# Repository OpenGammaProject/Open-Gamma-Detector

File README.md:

# Open Gamma Detector

---

**This is the latest hardware revision 4.2 using the Pico 2! For older revisions, please have a look at the [other branches](https://github.com/OpenGammaProject/Open-Gamma-Detector/branches). A comparison between the 4.0 and 3.x hardware can be found [here](https://hackaday.io/project/185211-all-in-one-gamma-ray-spectrometer/log/225597-revision-40-status-report).**

**This project is also on [Hackaday.io](https://hackaday.io/project/185211-all-in-one-gamma-ray-spectrometer), where I post important project updates and other announcements!**

Open hardware for a hackable gamma spectrometer all-in-one device using a popular NaI(Tl) scintillation crystal and a silicon photomultiplier (SiPM). Extremely affordable design for a powerful DIY gamma spectroscopy setup with a total parts cost of around 200 USD if you get all the individual parts and assemble them on your own.

The detector uses a standard serial-over-USB and hardware UART connections so that it can be integrated into as many other projects as possible, for example data logging with a Raspberry Pi, weather stations, Arduino projects, etc. It includes both scintillation counter and multichannel analyzer (MCA) functions depending on how you want to use it.

<p align="center">
  
  <br>
  
</p>

If you want a more barebones version of the Open Gamma Detector to only count pulses or similar, you can have a look at the [Mini SiPM Driver](https://github.com/OpenGammaProject/Mini-SiD) board.

## Features

Here are some of the most important specs:

- Compact design: Total size 120 x 50 mm. Approx. 70.5 x 50 mm area for electronics and additional 49.5 x 50 mm to mount a scintillator.
- All-in-one: No external parts (e.g. sound card) required to record gamma spectra.
- Standalone spectra recordings on built-in flash.
- Easily programmable using drag-and-drop firmware files or the standard Arduino IDE.
- Low-voltage device: No HV needed like with photomultiplier tubes.
- Can use SiPMs in the voltage range of 27.5 V to 33.8 V.
- 4096 ADC channels with built-in 3 V voltage reference.
- Energy resolution of up to 7% @ 662 keV possible; highly dependent on your SiPM/scintillator assembly.
- Energy Mode: ~10 µs total dead time while measuring energy (default settings).
- Geiger Mode: ~1 µs total dead time without energy measurements (default settings).
- Low power consumption: ~15 mA @ 5 V with default firmware at normal background.
- Built-in ticker (buzzer) for audible pulse count rate output.
- Additional broken-out power pins and I2C, SPI and UART headers for custom parts (e.g. display, µSD card, etc.).
- Simple OLED support out of the box (SSD1306 and SH110x).
- Built-in True Random Number Generator.

## How To Get One

- You can check out the project on PCBWay (affiliate) and if you buy through their service, it supports the project a little, and doesn’t cost you anything extra.
- Otherwise, use a PCB manufacturer and an electronics distributor of your choice and proceed on your own. All the files you'll need can be found in this repo.
- If you don't want to deal with all of that, feel free to contact me. Just send me an e-mail and I can help you out with the process.

**You will also need to buy a SiPM (e.g. the MICROFC-60035-SMT-TR) and scintillator (NaI(Tl) recommended) separately at a distributor of your choice.** You might also want to grab one of the countless SiPM breakout boards I made.

## Working Principle

Here is a nice flow chart to describe how the device roughly works:

## Hardware

Hardware design has been done with [EasyEDA](https://easyeda.com/) and all the needed files for you to import the project as well as the schematic can be found in the `hardware` folder. There is also a Gerber file available for you to go directly to the PCB manufacturing step.

Detailed information about the hardware of the detector as well as the potentiometer settings and assembly can be found in the [hardware directory](/hardware/).

## Software

The software aims to be as simple as possible to understand and maintain. To achieve this I decided to use an off-the-shelf microcontroller - the [Raspberry Pi Pico 2](https://www.raspberrypi.com/products/raspberry-pi-pico-2/). This board can be programmed with the Arduino IDE over micro-USB and is powerful (dual core, fast ADC, plenty of memory, ...) enough for the purpose and also exceptionally cheap.

To program the Pico 2 and/or play around with the firmware, head to the [software directory](/software/). There you will also find documentation on the serial interface (!), display support, and much more.

## Troubleshooting and FAQ

Please have a look at [REFERENCE.md](REFERENCE.md) for some general guidance.

If this doesn't help you, feel free to reach out and create an issue or open a discussions thread.

## Example Spectra

Here is a small collection of example spectra I could make quickly without putting much effort into the detector settings (threshold, SiPM voltage, software tweaks). I'm using the [Tiny MicroFC Breakout](https://github.com/OpenGammaProject/Tiny-MicroFC-Carrier-Board) and just a single SiPM (which isn't the optimal setup actually). In addition, neither the electronics nor the scintillator and sample were shielded from EMI or background radiation whatsoever. So as you can see the detector is actually pretty robust in that regard.

Background spectrum (2h) with no samples:

Spectrum (2h) of two tiny (~5 g) LYSO scintillator showing two distinct gamma peaks (201.83, 306.78 keV) with an additional ~55 keV X-ray peak. The 307 keV peak has an energy resolution of ~14% in this case:

Spectrum (5min) of Am-241 commonly used in household ionization smoke detectors (e.g. in the US, no longer in the EU). Gamma peaks at 26.34 and 59.54 keV:

Spectrum (2h) of a small tea cup with pure Uraninite (also known as pitchblende) contents in its glaze. You can see all kinds of isotopes of the Uranium series including the Bi-214 peak at ~610 keV. Because they just used the pure Uraninite without any filtering whatsoever, there is also some U-235 in it and all the daughter radionuclides as well:

Spectrum (30min) of a Na-22 test source, about ~2 µCi made with a Rev.2 board (worse energy resolution than the latest version). You can see the 511 keV annihilation peak and the small 1275 keV gamma peak (much smaller due to limited NaI efficiency and small scintillator size for this energy) as well as the compton edge and continuum:

Spectrum (2h) of about 100 grams of mushrooms still containing the isotope Cs-137 from the Chernobyl disaster. You can clearly see the gamma peak at 662 keV and the ~32 keV X-ray peak. Resolution of the 662 keV peak was ~8.6%, using only a single SiPM and an old NaI scintillator:

---

**Here are some of the same spectra using a larger 1x1 inch scintillator rated at 6.9% @ 662 keV and a 2x2 SiPM array:**

Spectrum (1h) of the same mushroom sample from above. This time the resolution at the 662 keV Cs-137 was 7.7%, not bad!

Spectrum (1h) of a small batch of Lutetium(III) oxide. It contains Lu-176 just like the LYSO scintillator sample from above. Therefore it also has the same peaks, just a lot more clear now. The 307 keV peak now has an energy resolution of 11.5%.

## Known Limitations

1. ~~The Raspberry Pi Pico's ADC has some pretty [severe DNL issues](https://pico-adc.markomo.me/INL-DNL/#dnl) that result in four channels being much more sensitive (wider input range) than the rest. For now the simplest solution was to discard all four of them, by printing a `0` when any of them comes up in the measurement (to not affect the cps readings). You can turn this behavior off by using the `set correction` command. This is by no means perfect or ideal, but it works for now until this gets fixed in a later hardware revision of the RP2040 (wish us luck!).~~ Fixed by the Pico 2!
2. The power supply is **not** temperature corrected itself, meaning changes in the ambient temperature with a constant voltage affect the gain of the SiPM. This will naturally result in a different DC bias, energy range and S/N ratio. This effect is negligible around room temperature, though. The temperature dependence of the gain is -0.8%/°C (21°C) for the MicroFC SiPMs. **The latest [MicroFC SiPM carrier board](https://github.com/OpenGammaProject/MicroFC-SiPM-Carrier-Board) has automatic temperature compensation on-board however! So use that if you want to get the best performance out of it.**

## Some Ideas

### Coincidence Measurements

Using multiple detector boards with some firmware modifications it should be theoretically possible to implement a coincidence measurement feature. By respectively connecting the `VSYS`, `GND` and one of the broken-out pins to each other on both boards you have everything you need to get started. The pins would be used for an interrupt from the child detector to the parent to trigger a pulse if both timings coincide.

At the moment, though, I couldn't get a coincidence mode feature running due to some weird timing issues. There might be a firmware update in the future to implement this feature. If you have any ideas, let me know!

### Cooling the SiPM

During operation all the electronics including the SiPM naturally heat up ever so slightly. Due to the detector board (where most of the power is dissipated) not being directly connected to the SiPM self-heating is negligible, though. Therefore air or water cooling alone won't improve performance considerably, because it won't heat up much above ambient temps, if at all that is. However, you could cool the SiPM PCB with a Peltier module to sub-ambient temperatures. According to the [datasheet AND9770 (Figure 27)](https://www.onsemi.com/pub/Collateral/AND9770-D.PDF) every 10°C reduction in temperature decreases the dark count rate by 50%! But be sure to correct the SiPM voltage (overvoltage) in this case as it also changes with temperature.

Note that the required breakdown voltage of the SiPM increases linearly with 21.5 mV/°C, see the [C-Series SiPM Sensors Datasheet](https://www.onsemi.com/pdf/datasheet/microc-series-d.pdf). This means that you would also need to temperature correct the PSU voltage if you wanted to use it with considerably different temperatures.

### Shielding Background Radiation

Shielding the ambient background can be done ideally using a wide enough layer of lead (bricks) all around the detector with a thin layer of lower-Z material on the inside such as copper to avoid backscattering. The SiPM and the sample can then be put into the structure to get the best measurements possible (low background).

See Wikipedia: [Lead Castle](https://en.wikipedia.org/w/index.php?title=Lead_castle&oldid=991799816)

## Related Projects

This is a list of other awesome projects that are relevant or directly related to this one:

- [OpenDosimeter](https://opendosimeter.org/): A low-cost dosimeter with open-source hardware and software inspired heavily by the Open Gamma Detector.
- [CosmicWatch](http://www.cosmicwatch.lns.mit.edu/): A neat all-in-one device to detect muons. Completely open-source and designed for university students and schools. This project was the original inspiration to start with the Open Gamma Project.
- [OpenGammaKit](https://github.com/vikulin/OpenGammaKit/): Re-design of the Open Gamma Detector hardware using KiCAD, with additionally updated software for mobile use.

Check them out and let me know what you think. Special thanks to all of the contributors and the entire community for making this possible!

---

Thanks for reading.

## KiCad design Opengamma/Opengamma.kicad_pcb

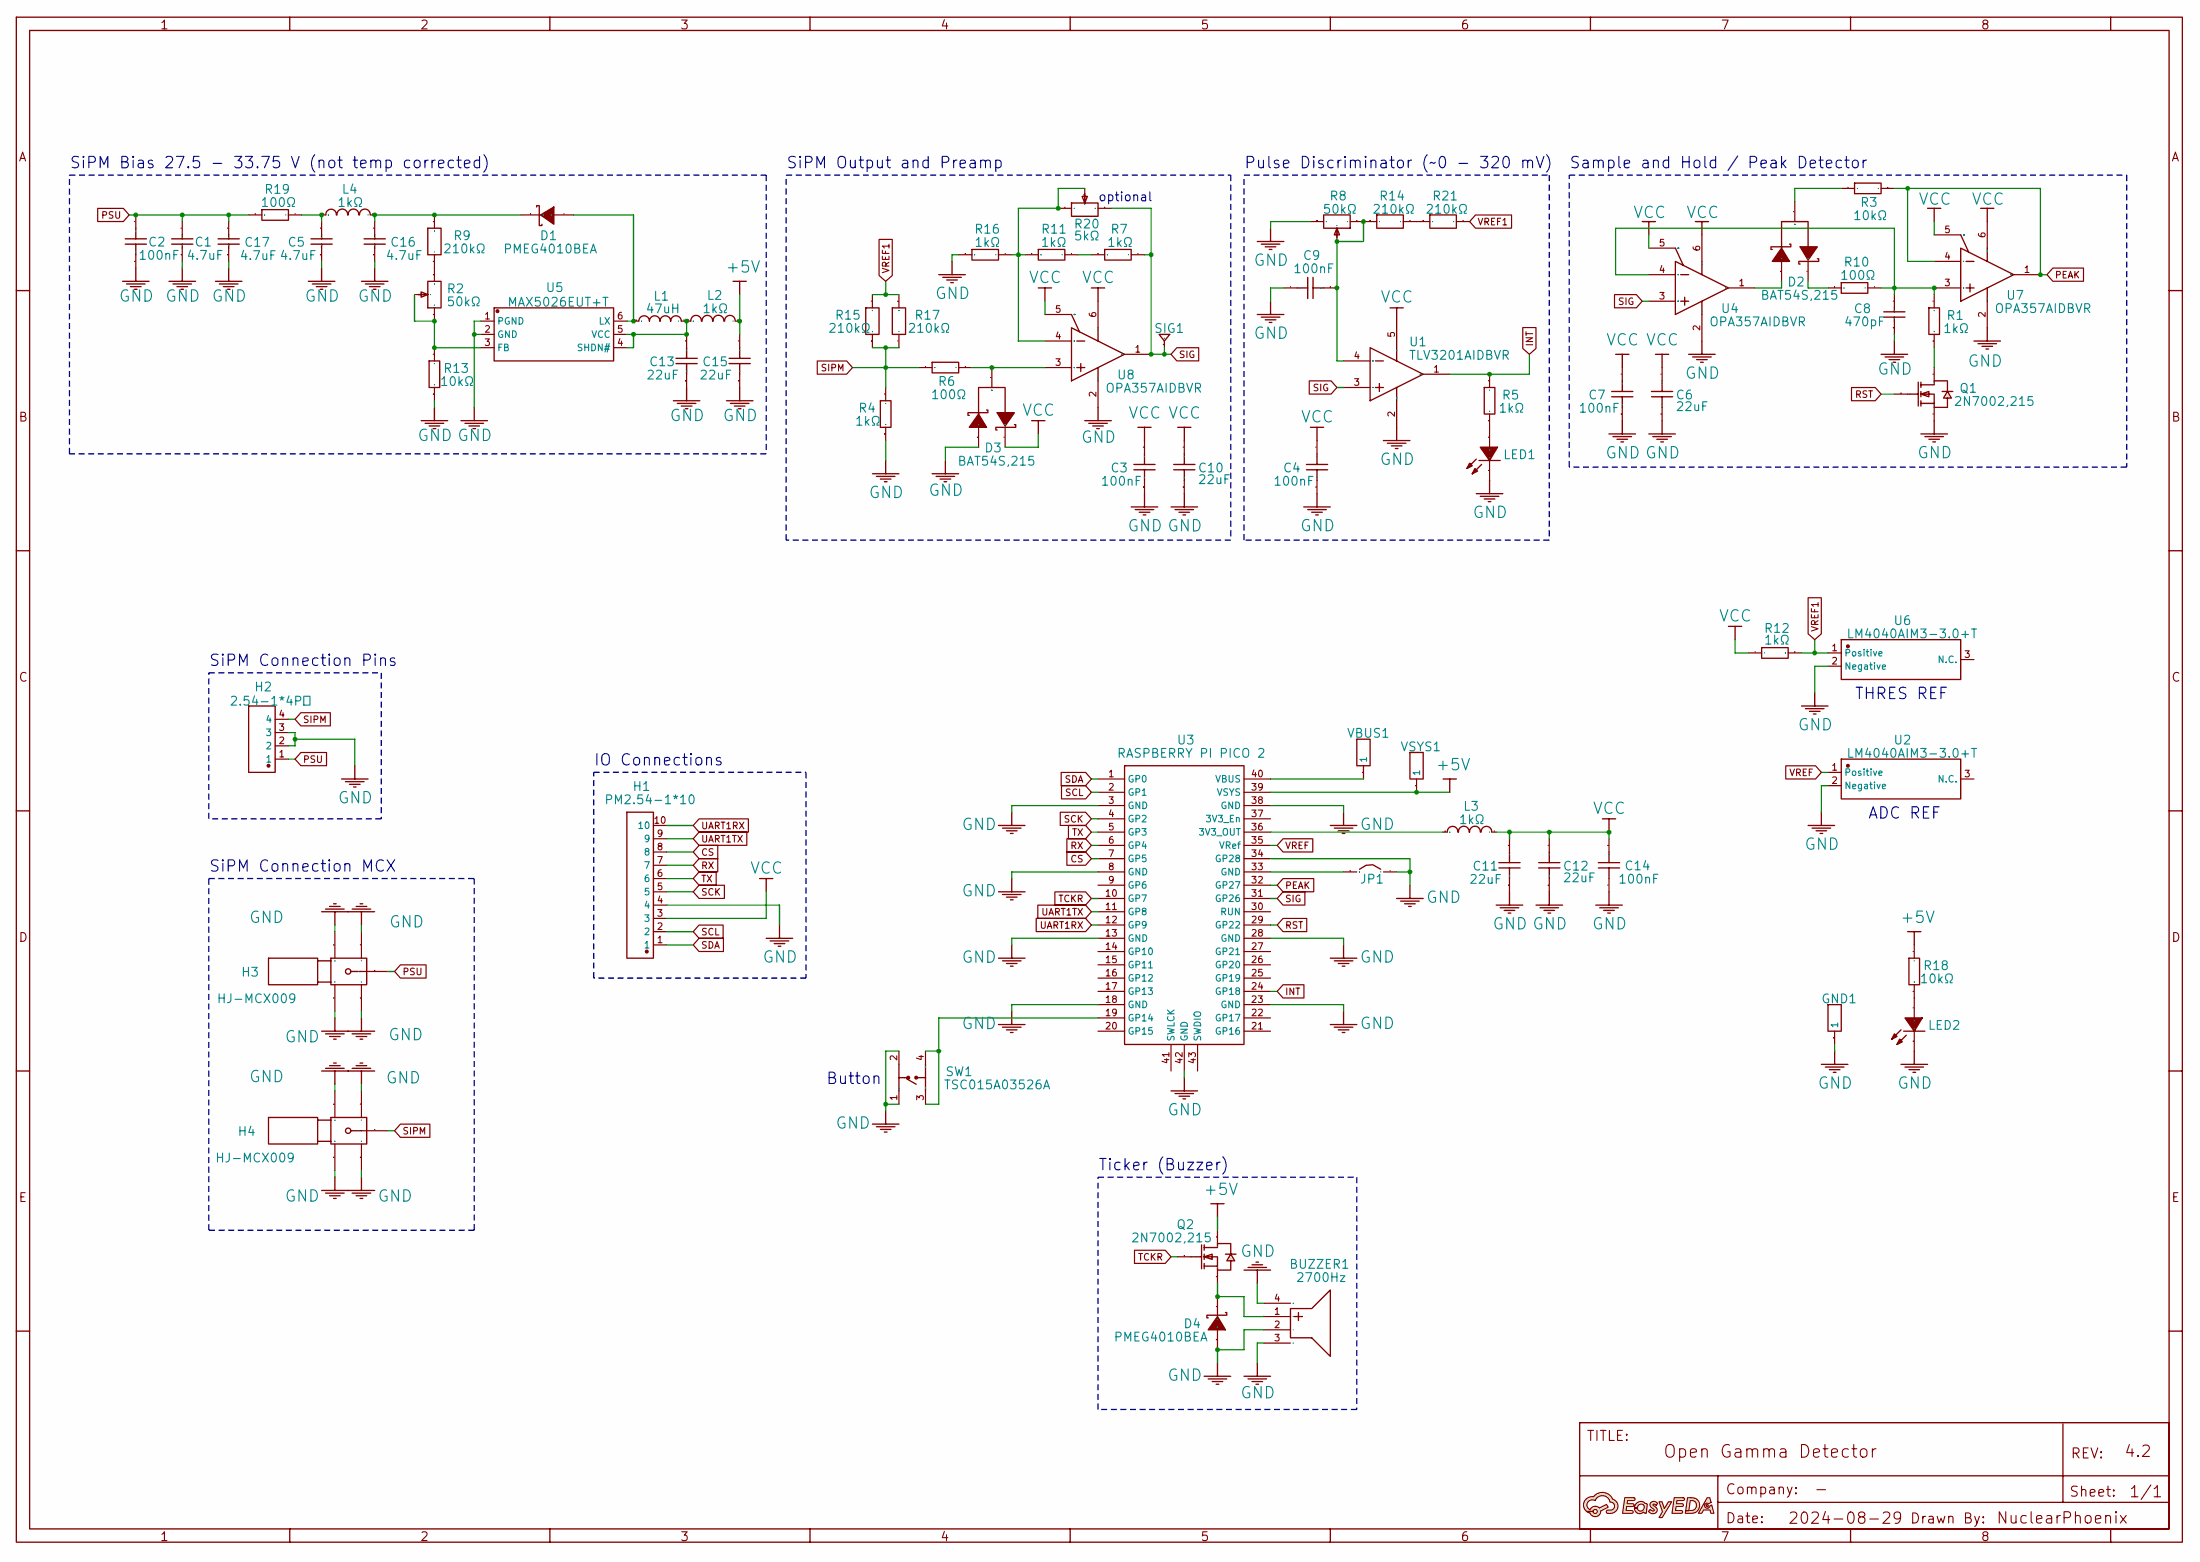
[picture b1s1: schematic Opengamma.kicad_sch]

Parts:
BUZZER1: 2700Hz; Manufacturer Part MLT-7525
C1, C5, C16, C17: 4.7uF; Manufacturer Part CL21A475KBQNNNE
C2, C3, C4, C7, C9, C14: 100nF; Manufacturer Part CL10B104KC8NNNC
C6, C10, C11, C12, C13, C15: 22uF; Manufacturer Part CL10A226MP8NUNE
C8: 470pF; Manufacturer Part ECHU1C471JX5
D1, D4: PMEG4010BEA; Manufacturer Part PMEG4010BEA,115
D2, D3: BAT54S,215; Manufacturer Part BAT54S,215
GND1: HDR-M-2.54_1x1
H1: PM2.54-1*10; Manufacturer Part PM2.54-1*10
H2: 2.54-1*4P母; Manufacturer Part 2.54-1*4P母
H3, H4: HJ-MCX009; Manufacturer Part HJ-MCX009
JP1: Jumper
L1: 47uH; Manufacturer Part NRS4018T470MDGJ
L2, L3, L4: 1kΩ; Manufacturer Part BLM18KG102SN1D
LED1, LED2: LTST-C190KGKT; Manufacturer Part LTST-C190KGKT
NO1: NO; Manufacturer Part ?
Q1, Q2: 2N7002,215; Manufacturer Part 2N7002,215
R1, R4, R5, R7, R11, R12, R16: 1kΩ; Manufacturer Part ARG03BTC1001
R2, R8: 50kΩ; Manufacturer Part 3296W-1-503LF
R3, R13, R18: 10kΩ; Manufacturer Part ARG03FTC1002
R6, R10, R19: 100Ω; Manufacturer Part 0603WAF1000T5E
R9, R14, R15, R17, R21: 210kΩ; Manufacturer Part TC0325D2103T5H
R20: 5kΩ; Manufacturer Part 3314J-1-502E
SIG1: TEST-POINT
SW1: TSC015A03526A; Manufacturer Part TSC015A03526A
U1: TLV3201AIDBVR; Manufacturer Part TLV3201AIDBVR
U2, U6: LM4040AIM3-3.0+T; Manufacturer Part LM4040AIM3-3.0+T
U3: RASPBERRY PI PICO 2; Manufacturer Part SC1631
U4, U7, U8: OPA357AIDBVR; Manufacturer Part OPA357AIDBVR
U5: MAX5026EUT+T; Manufacturer Part MAX5026EUT+T
VBUS1: HDR-M-2.54_1x1
VSYS1: HDR-M-2.54_1x1

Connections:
+5V: C15.2, L2.2, Q2.3 (D), R18.2, U3.39 (VSYS), VSYS1.1
CS: H1.8, U3.7 (GP5)
GND: BUZZER1.2 (-), BUZZER1.3, BUZZER1.4, C1.1, C2.1, C3.1, C4.1, C5.1, C6.1, C7.1, C8.1, C9.2, C10.1, C11.1, C12.1, C13.1, C14.2, C15.1, C16.1, C17.1, D3.1 (A), D4.2 (A), GND1.1, H1.4, H2.2, H2.3, H3.1, H3.2, H3.3, H3.4, H4.1, H4.2, H4.3, H4.4, JP1.2, LED1.1 (-), LED2.1 (-), Q1.2 (S), R4.1, R8.1, R13.1, R16.1, SW1.1, SW1.2, U1.2 (GND), U2.2 (Negative), U3.3 (GND), U3.8 (GND), U3.13 (GND), U3.18 (GND), U3.23 (GND), U3.28 (GND), U3.34 (GP28), U3.38 (GND), U3.42 (GND), U4.2 (V-), U5.1 (PGND), U5.2 (GND), U6.2 (Negative), U7.2 (V-), U8.2 (V-)
INT: R5.2, U1.1 (OUT), U3.24 (GP18)
unnamed: BUZZER1.1 (+), D4.1 (K), Q2.2 (S)
unnamed: C5.2, L4.1, R19.2
unnamed: D1.2 (A), L1.1, U5.6 (LX)
unnamed: C16.2, D1.1 (K), L4.2, R9.1
unnamed: D2.1 (A), U4.1 (OUT)
unnamed: D2.3 (AK), R3.2
unnamed: D2.2 (K), R10.1
unnamed: D3.3 (AK), R6.2, U8.3 (IN+)
unnamed: JP1.1, U3.33 (GND)
unnamed: LED1.2 (+), R5.1
unnamed: LED2.2 (+), R18.1
unnamed: Q1.3 (D), R1.1
unnamed: R2.1, R9.2
unnamed: R7.1, R11.2
unnamed: R14.2, R21.1
unnamed: C9.1, R8.2, R8.3, R14.1, U1.4 (IN-)
unnamed: L3.1, U3.36 (3V3_OUT)
unnamed: SW1.3, SW1.4, U3.19 (GP14)
unnamed: U3.40 (VBUS), VBUS1.1
unnamed: C8.2, R1.2, R10.2, U4.4 (IN-), U7.3 (IN+)
unnamed: R2.2, R2.3, R13.2, U5.3 (FB)
unnamed: C13.2, L1.2, L2.1, U5.4 (SHDN#), U5.5 (VCC)
unnamed: R11.1, R16.2, R20.2, R20.3, U8.4 (IN-)
PEAK: R3.1, U3.32 (GP27), U7.1 (OUT), U7.4 (IN-)
PSU: C1.2, C2.2, C17.2, H2.1, H3.5, R19.1
RST: Q1.1 (G), U3.29 (GP22)
RX: H1.7, U3.6 (GP4)
SCK: H1.5, U3.4 (GP2)
SCL: H1.2, U3.2 (GP1)
SDA: H1.1, U3.1 (GP0)
SIG: R7.2, R20.1, SIG1.1, U1.3 (IN+), U3.31 (GP26), U4.3 (IN+), U8.1 (OUT)
SIPM: H2.4, H4.5, R4.2, R6.1, R15.1, R17.2
TCKR: Q2.1 (G), U3.10 (GP7)
TX: H1.6, U3.5 (GP3)
UART1RX: H1.10, U3.12 (GP9)
UART1TX: H1.9, U3.11 (GP8)
VCC: C3.2, C4.2, C6.2, C7.2, C10.2, C11.2, C12.2, C14.1, D3.2 (K), H1.3, L3.2, R12.2, U1.5 (VCC), U4.5 (ENABLE), U4.6 (V+), U7.5 (ENABLE), U7.6 (V+), U8.5 (ENABLE), U8.6 (V+)
VREF: U2.1 (Positive), U3.35 (VRef)
VREF1: R12.1, R15.2, R17.1, R21.2, U6.1 (Positive)

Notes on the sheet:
SiPM Bias 27.5 - 33.75 V (not temp corrected)
THRES REF
SiPM Connection MCX
optional
Button
Pulse Discriminator (~0 - 320 mV)
SiPM Connection Pins
SiPM Output and Preamp
Ticker (Buzzer)
ADC REF
Sample and Hold / Peak Detector
IO Connections

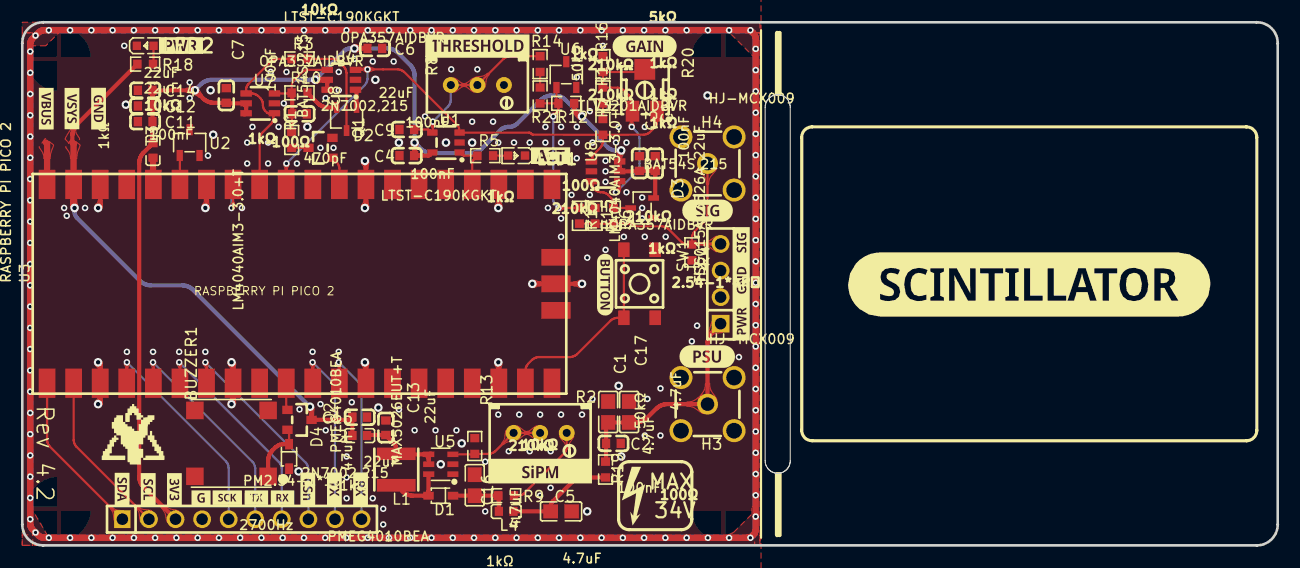
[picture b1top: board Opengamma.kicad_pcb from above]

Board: 2 copper layers, 120.0 x 50.0 mm, 65 parts (1 on the bottom side), 42 nets.

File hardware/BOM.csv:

ID;Name;Designator;Footprint;Quantity;Manufacturer Part;Manufacturer;Supplier;Supplier Part;Price
1;2700Hz;BUZZER1;BUZ-SMD_4P-L7.5-W7.5-P7.59-TL;1;MLT-7525;华能;LCSC;C95299;0.226
2;PMEG4010BEA;D1,D4;SOD-323_L1.8-W1.3-LS2.5-RD;2;PMEG4010BEA,115;Nexperia(安世);LCSC;C36975;1.315
3;PM2.54-1*10;H1;HDR-TH_10P-P2.54-V-F;1;PM2.54-1*10;ZHOURI(洲日);LCSC;C5116489;0.106
4;2.54-1*4P母;H2;HDR-TH_4P-P2.54-V-F;1;2.54-1*4P母;BOOMELE(博穆精密);LCSC;C2718488;0.047
5;HJ-MCX009;H3,H4;ANT-TH_L6.0-W6.0_MCX-KE;2;HJ-MCX009;皇捷;LCSC;C2904906;0.724
6;47uH;L1;IND-SMD_L4.0-W4.0_NR4018T;1;NRS4018T470MDGJ;TAIYO YUDEN(太诱);LCSC;C222886;0.126
7;2N7002,215;Q1,Q2;SOT-23_L2.9-W1.3-P1.90-LS2.4-BR;2;2N7002,215;Nexperia(安世);LCSC;C65189;0.161
8;1kΩ;R1,R4,R5,R7,R11,R12,R16;R0603;7;ARG03BTC1001;Viking(光颉);LCSC;C309080;0.019
9;100Ω;R6,R10,R19;R0603;3;0603WAF1000T5E;UNI-ROYAL(厚声);LCSC;C22775;0.001
10;210kΩ;R9,R14,R15,R17,R21;R0603;5;TC0325D2103T5H;UNI-ROYAL(厚声);LCSC;C517422;0.023
11;TSC015A03526A;SW1;SW-SMD_4P-L4.5-W4.5-P3.00-LS6.8;1;TSC015A03526A;BZCN(博众电气);LCSC;C2888900;0.011
12;TLV3201AIDBVR;U1;SOT-23-5_L3.0-W1.7-P0.95-LS2.8-BR;1;TLV3201AIDBVR;TI(德州仪器);LCSC;C105188;0.402
13;LM4040AIM3-3.0+T;U2,U6;SOT-23-3_L2.9-W1.6-P1.90-LS2.8-BR;2;LM4040AIM3-3.0+T;ADI(亚德诺)/MAXIM(美信);LCSC;C143326;1.381
14;RASPBERRY PI PICO 2;U3;PI-PICO-SMD;1;SC1631;Raspberry Pi;Mouser;358-SC1631;
15;4.7uF;C1,C5,C16,C17;C0805;4;CL21A475KBQNNNE;SAMSUNG(三星);LCSC;C98192;0.02
16;BAT54S,215;D2,D3;SOT-23-3_L3.0-W1.7-P0.95-LS2.9-BR;2;BAT54S,215;Nexperia(安世);LCSC;C47546;0.016
17;LTST-C190KGKT;LED1,LED2;LED0603-RD;2;LTST-C190KGKT;LITEON(光宝);LCSC;C125094;0.015
18;10kΩ;R3,R13,R18;R0603;3;ARG03FTC1002;Viking(光颉);LCSC;C217687;0.007
19;22uF;C6,C10,C11,C12,C13,C15;C0603;6;CL10A226MP8NUNE;SAMSUNG(三星);LCSC;C86295;0.015
20;100nF;C2,C3,C4,C7,C9,C14;C0603;6;CL10B104KC8NNNC;SAMSUNG(三星);LCSC;C15725;0.006
21;50kΩ;R2,R8;RES-ADJ-TH_3296W;2;3296W-1-503LF;BOURNS;LCSC;C83686;0.712
22;OPA357AIDBVR;U4,U7,U8;SOT-23-6_L2.9-W1.6-P0.95-LS2.8-BR;3;OPA357AIDBVR;TI(德州仪器);LCSC;C139385;1.568
23;MAX5026EUT+T;U5;SOT-23-6_L2.9-W1.6-P0.95-LS2.8-BL;1;MAX5026EUT+T;ADI(亚德诺)/MAXIM(美信);LCSC;C87603;1.696
24;470pF;C8;C0603;1;ECHU1C471JX5;PANASONIC(松下);LCSC;C178419;0.262
25;1kΩ;L2,L3,L4;L0603;3;BLM18KG102SN1D;muRata(村田);LCSC;C160982;0.017

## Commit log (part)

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2020-10-18 add hardware files
2020-10-18 move hardware
2020-10-18 add some info
2020-10-18 add software
2020-11-02 add content sections
2020-11-08 Create placeholder
2020-11-08 add files
2020-11-08 add python requirements
2020-11-08 format python scripts
2020-11-08 add software info
2020-12-25 add background shielding + cooling sections
2021-04-18 add very simple serial interface
2021-04-18 misc working changes
2021-05-11 cleanup and simplify detector software
2021-05-11 cleanup
2021-05-13 revert stupid change
2021-07-21 add disclaimer
2021-09-21 add raspberry pi pico note
2021-10-18 add chart
2021-10-20 fix for dark mode
2021-11-20 add pico script
2021-11-20 remove python scripts
2021-11-20 rename
2021-11-20 update text
2021-11-20 update software
2021-11-20 add teaser image
2021-12-03 add badge
2021-12-04 [ImgBot] Optimize images
    *Total -- 119.67kb -> 82.81kb (30.8%)
    /docs/lu-176.png -- 70.65kb -> 42.60kb (39.7%)
    /docs/flow.drawio.png -- 49.01kb -> 40.21kb (17.96%)
2021-12-04 update plot
2022-02-22 update detector files
2022-02-22 new SiPM mount files
2022-02-23 [ImgBot] Optimize images
    *Total -- 320.89kb -> 171.71kb (46.49%)
    /docs/am-241.png -- 56.62kb -> 23.46kb (58.57%)
    /docs/pcb_back.png -- 59.97kb -> 32.17kb (46.35%)
    /docs/lu-176.png -- 78.05kb -> 44.23kb (43.34%)
    /docs/pcb_front.png -- 126.26kb -> 71.85kb (43.09%)
2022-02-23 [ImgBot] Optimize images
    /docs/flow.drawio.png -- 35.64kb -> 12.09kb (66.08%)
2022-02-23 remove gitignore
2022-02-24 add EOL char for Gamma MCA
2022-02-27 add scintillator assembly
2022-02-27 add key features
2022-03-06 add spectrum
2022-03-07 change img layout
2022-03-26 add serial commands
2022-04-01 add geiger mode
2022-04-14 misc event code changes
2022-04-14 discard non-linear adc values due to dnl
2022-04-18 set max pin output current
2022-04-23 add DNL issue
2022-05-07 small fixes
2022-05-07 new SiPM carrier board!
2022-05-16 remove SiPM carrier hardware
    moved to https://github.com/Open-Gamma-Project/SiPM-Carrier-Board
2022-06-30 update hackaday info
2022-07-01 misc layout and text changes
2022-07-01 add use cases
2022-07-01 fix firmware name
2022-07-01 slight changes in DNL note
2022-07-02 small misc changes
2022-07-03 unzip gerber
2022-07-03 Use UTF-8 encoding on BOM.csv
    Kitspace can't deal with UTF-16 BOMs yet
2022-07-04 fix cps buffer overflowing and crashing
2022-07-05 change pins for new board rev
2022-07-05 board revision 2
2022-07-05 update LYSO spectrum
2022-07-05 add remark on PCB size
2022-07-05 [ImgBot] Optimize images
    *Total -- 273.98kb -> 140.26kb (48.81%)
    /docs/flow.drawio.png -- 33.33kb -> 10.44kb (68.69%)
    /docs/pcb_back.png -- 48.30kb -> 22.79kb (52.81%)
    /docs/pcb_front.png -- 126.35kb -> 69.95kb (44.64%)
    /docs/lu-176.png -- 65.99kb -> 37.08kb (43.81%)
2022-07-08 add assembled boards note
2022-07-08 add background spectrum
2022-07-08 add space
2022-07-09 [ImgBot] Optimize images
    *Total -- 130.94kb -> 76.33kb (41.71%)
    /docs/bg.png -- 61.04kb -> 34.73kb (43.11%)
    /docs/lu-176-new.png -- 69.90kb -> 41.60kb (40.48%)
2022-07-30 add optional parts info
2022-08-13 Clarify issue #15
2022-08-18 version 2.1.0
    changelog:
    - remove unused Arduino Pico Analog Correction lib
    - add auto resets of the S&H circuit to help with 50 HZ mains
    interference when not shielded
    - small misc changes
2022-08-18 update detector commands
2022-08-19 remove compiled file
    oops
2022-08-19 slight revision changes
    Changelog:
    - Change inductor orientation for best EMI
    - R3 is now 1k! This fixes an old issue with noise at low energies
    - "Optional" parts markings in the schematic
    - New spectra
    - New images
2022-08-19 fix tab
2022-08-24 firmware v2.2.0
    changelog:
    - persistent settings: saving and loading from flash
    - add command to reset the settings
    - more detailed serial command interactions
    - fix temperature readings
    - add setting for the meas averaging
2022-08-25 add link to shop page
2022-09-02 add image for poti controls
2022-09-22 fix encoding
2022-09-22 add hardware watchdog
2022-09-26 update external shops and links
2022-09-29 add new image
2022-09-29 clarify dead time
2022-09-30 fix URL
2022-10-09 add Na-22 spectrum
2022-10-09 add coincidence mode section
2022-10-09 [ImgBot] Optimize images
    *Total -- 1,170.45kb -> 1,077.26kb (7.96%)
    /docs/na-22.png -- 58.01kb -> 32.49kb (44%)
    /docs/controls.jpg -- 123.30kb -> 115.03kb (6.71%)
    /docs/img2.jpg -- 989.14kb -> 929.74kb (6.01%)
2022-10-15 add oled support
2022-10-15 punctuation
2022-10-16 auto refresh oled data
2022-10-17 add display command
2022-10-26 bump firmware
2022-10-26 add firmware files
2022-10-28 add UF2 with 3.0 voltage reference
2022-11-02 add new todo
2022-11-02 small grammar changes and typos
2022-11-05 add overclocked pico firmware
2022-11-05 add sipm to intro text
2022-11-07 - fix crashes after some time with auto-enabled display, which would activate although there's not display
    - fix events not added in geiger mode
2022-11-07 autoformat
2022-11-12 faster display refresh
2022-11-12 FW version 2.3.4
2022-11-21 add 3D print case files
2022-11-21 add attribution
2022-11-21 add 3D-printable enclosure text
2022-11-21 add link to ViewSTL
2022-11-27 Firmware update 2.4.0
    - Add True Random Number Generator.
    - Add function to read settings.
    - Move meta-data reading (like temperature, Vsys, etc.) to "read info"
    command.
2022-11-27 fix indentation
2022-12-01 add reduced height versions
2022-12-01 TRNG disclaimer
2022-12-03 FW Update 2.5.0
    Changelog:
    - Change SimpleShell to SimpleShell_Enhanced
    - Complete Serial shell re-design
    - Add TRNG number storage
    - Add delay time serial setting
    - Some other small misc changes
2022-12-03 fix default vref
2022-12-03 add display issue link
2022-12-04 add dead time to info
2022-12-04 change fsinfo stats
2022-12-17 fix Vref
2022-12-21 [ImgBot] Optimize images
    *Total -- 193.16kb -> 170.79kb (11.58%)
    /docs/gamma_mca.png -- 101.91kb -> 83.30kb (18.26%)
    /docs/inside_box.jpg -- 91.25kb -> 87.49kb (4.12%)
2022-12-21 add tindie store link
2022-12-21 add OSHW cert badge
2022-12-30 add FW 2.5.2 files
2023-01-11 Stop filtering out PCB services in kitspace.yaml
2023-01-16 Fix URLs
2023-02-05 move oshwa link
2023-02-19 Fix display crashes
    Problem was the event_int function was possibly using the ADC _while_ the temp reading was going and this crashed the device.
2023-02-19 switch to bool
    Programmed too much in TS LOL
2023-02-19 FW version 2.5.3
2023-02-19 remove old FW files
2023-02-22 add total cost estimate
2023-02-26 enable strict checking
2023-03-01 FW for HW Rev 3.0
2023-03-01 add degree symbol
2023-03-08 hardware revision 3
2023-04-07 change intro text
2023-04-10 Fix #31
    Add Adafruit lib
2023-04-11 re-add image
2023-04-11 minor fixes
2023-04-11 add FW files
2023-04-11 update images
2023-04-11 remove space
2023-04-11 fix line break
2023-04-12 fix spectra description
    Some errors and old info
2023-04-12 add comparison post
2023-04-12 Update text on SiPM/scintillator size
2023-04-12 add OLED image
2023-04-16 update some comments
2023-04-16 update thumbnails
2023-04-18 add ring buffer for display cps
2023-04-18 fix comment
2023-04-19 update OSHWA cert
2023-04-19 [ImgBot] Optimize images
    *Total -- 3,574.95kb -> 3,155.38kb (11.74%)
    /docs/pcb_back.png -- 58.65kb -> 29.79kb (49.2%)
    /docs/pcb_front.png -- 109.66kb -> 58.35kb (46.79%)
    /docs/am-241.png -- 52.39kb -> 28.76kb (45.11%)
    /docs/bg.png -- 57.18kb -> 32.95kb (42.39%)
    /docs/glaze.png -- 63.96kb -> 38.20kb (40.27%)
2023-04-20 add 3D files
2023-04-21 Add Mini SiD reference
2023-04-21 FW 3.1.0
2023-04-22 Fixed typos, added link to vendors
2023-04-27 add array board references
2023-04-27 try to improve INT performance
2023-04-27 add BOOTSEL button switch
2023-04-29 FW 3.2.0
2023-04-29 update UF2 files
2023-05-06 add FW version 3.2.1
2023-05-15 add ticker feature
    also add debug info such as power-on hours and power cycles
2023-05-15 add v3.3.0 FW files
2023-05-15 add example ticker setting
2023-05-18 decrease buffer load
2023-05-18 add new FW files
2023-05-18 default SSD1306 display
2023-06-03 add Gamma MCA video
2023-06-07 convert text to SVG
2023-06-07 [ImgBot] Optimize images
    /docs/flow.drawio.svg -- 155.78kb -> 127.93kb (17.88%)
2023-07-06 update todo list
    there will be some changes soon ;)
2023-07-07 add FW 3.5.0 files
2023-07-07 add OpenGamma logo
2023-07-07 upload fixed FW files
2023-07-23 add version 3.5.1
2023-07-23 drop statistical, long live RunningMedian
2023-07-26 add temp compensation
2023-08-16 change 'read spectrum' output
2023-08-16 upload FW version 3.5.2
2023-08-19 add new case
2023-09-13 [ImgBot] Optimize images
    *Total -- 14,391.29kb -> 13,527.97kb (6%)
    /docs/mushrooms.png -- 74.44kb -> 46.51kb (37.53%)
    /docs/oshw.svg -- 13.54kb -> 12.54kb (7.39%)
    /docs/enclosure_empty2.jpg -- 3,407.81kb -> 3,201.28kb (6.06%)
    /docs/enclosure_panel1.jpg -- 3,524.37kb -> 3,311.37kb (6.04%)
    /docs/enclosure_empty1.jpg -- 3,478.40kb -> 3,268.17kb (6.04%)
2023-09-19 decrease OSHW size
2023-11-27 add rev 4 alpha sketch
2023-11-27 update screenshots to rev 4
2023-11-28 add hackaday posts
2023-12-02 add rev 4 to compat list
2023-12-02 update HW README
2023-12-02 add section on the onboard ACT LED
2023-12-02 update reference
2023-12-02 fix command description
2023-12-02 add FW 4.0.0 files
2023-12-02 rename files
2023-12-02 fix wrong state PS_PIN
2023-12-02 update software README
2023-12-02 update path
2023-12-02 add image caption
2023-12-02 update disclaimer
2023-12-03 update example spectra
2023-12-03 update uraninite desc
2023-12-03 [ImgBot] Optimize images
    *Total -- 666.42kb -> 400.29kb (39.93%)
    /docs/pcb_back.png -- 81.95kb -> 44.19kb (46.08%)
    /docs/am-241.png -- 47.93kb -> 26.76kb (44.18%)
    /docs/pcb_front.png -- 117.35kb -> 67.66kb (42.34%)
    /docs/bg.png -- 53.93kb -> 31.23kb (42.09%)
    /docs/lu-176.png -- 69.06kb -> 41.59kb (39.77%)
2023-12-06 change default averaging value
2023-12-06 bump version
2023-12-09 update OSHWA mark
2023-12-09 improve spectrometer response at high count rates
2023-12-10 misc changes
2023-12-27 add higher res spectra
2024-01-03 update ArduinoJSON support
2024-01-14 add notes on SiPM connection
2024-01-16 [ImgBot] Optimize images
    *Total -- 1,241.80kb -> 1,043.24kb (15.99%)
    /docs/pcb_back.png -- 80.57kb -> 42.92kb (46.73%)
    /docs/bg.png -- 58.20kb -> 34.59kb (40.57%)
    /docs/lu-176-advanced.png -- 57.14kb -> 34.80kb (39.09%)
    /docs/mushrooms.png -- 70.65kb -> 43.78kb (38.04%)
    /docs/mushrooms-advanced.png -- 57.21kb -> 35.76kb (37.49%)
2024-01-17 add info about buttons
2024-01-17 update specs
2024-01-17 add press duration
2024-01-18 update photos
2024-01-18 remove todo
2024-01-18 Remove part shortage limitation
2024-01-19 add FS spectrum recordings
2024-01-20 remove old comments
2024-01-20 add 4.2.0 FW files
2024-01-21 ignore build dir
2024-01-21 optimize if statements
2024-01-21 optimize adc bin number
2024-02-01 add note on forward compat to rev 4
2024-02-01 fix formatting
2024-02-02 add recording space warning
2024-02-26 fix #53
2024-03-02 update description
2024-03-04 add display default state note
2024-03-14 Update notes on saturation and the ACT LED
2024-03-29 add rev 4.1 files
2024-03-29 [ImgBot] Optimize images
    *Total -- 341.75kb -> 199.00kb (41.77%)
    /docs/pcb_back.png -- 81.21kb -> 43.25kb (46.74%)
    /docs/pcb_front.png -- 131.72kb -> 74.37kb (43.54%)
    /docs/controls.png -- 128.82kb -> 81.38kb (36.82%)
2024-06-04 add email support note
2024-06-05 add FW 4.2.2
    No changes, only updated arduino-pico for the latest LittleFS (file system) version.
2024-08-10 add Na-22 spectrum duration
2024-08-29 update HW files
2024-08-29 update README for Pico 2
2024-10-29 update firmware to 4.3.1
    - add reset reason to info screen
    - updated to latest arduino-pico
2024-11-18 update firmware to 4.3.2
    - minor fixes to the TRNG code
    - reduce overlock image frequency to 225
    - update ArduinoJSON and arduino-pico
    - Disable unused Serial1 (UART0)
2025-02-22 add pick and place file
2025-02-22 update kitspace
2025-04-09 add relevant projects
2025-11-10 add PCBWay affiliate
2025-11-10 rebuild fw with latest deps
2025-11-10 fix BOM UTF-8
2026-01-29 Add Open_Gamma_Detector project files (hardware, docs, software)
